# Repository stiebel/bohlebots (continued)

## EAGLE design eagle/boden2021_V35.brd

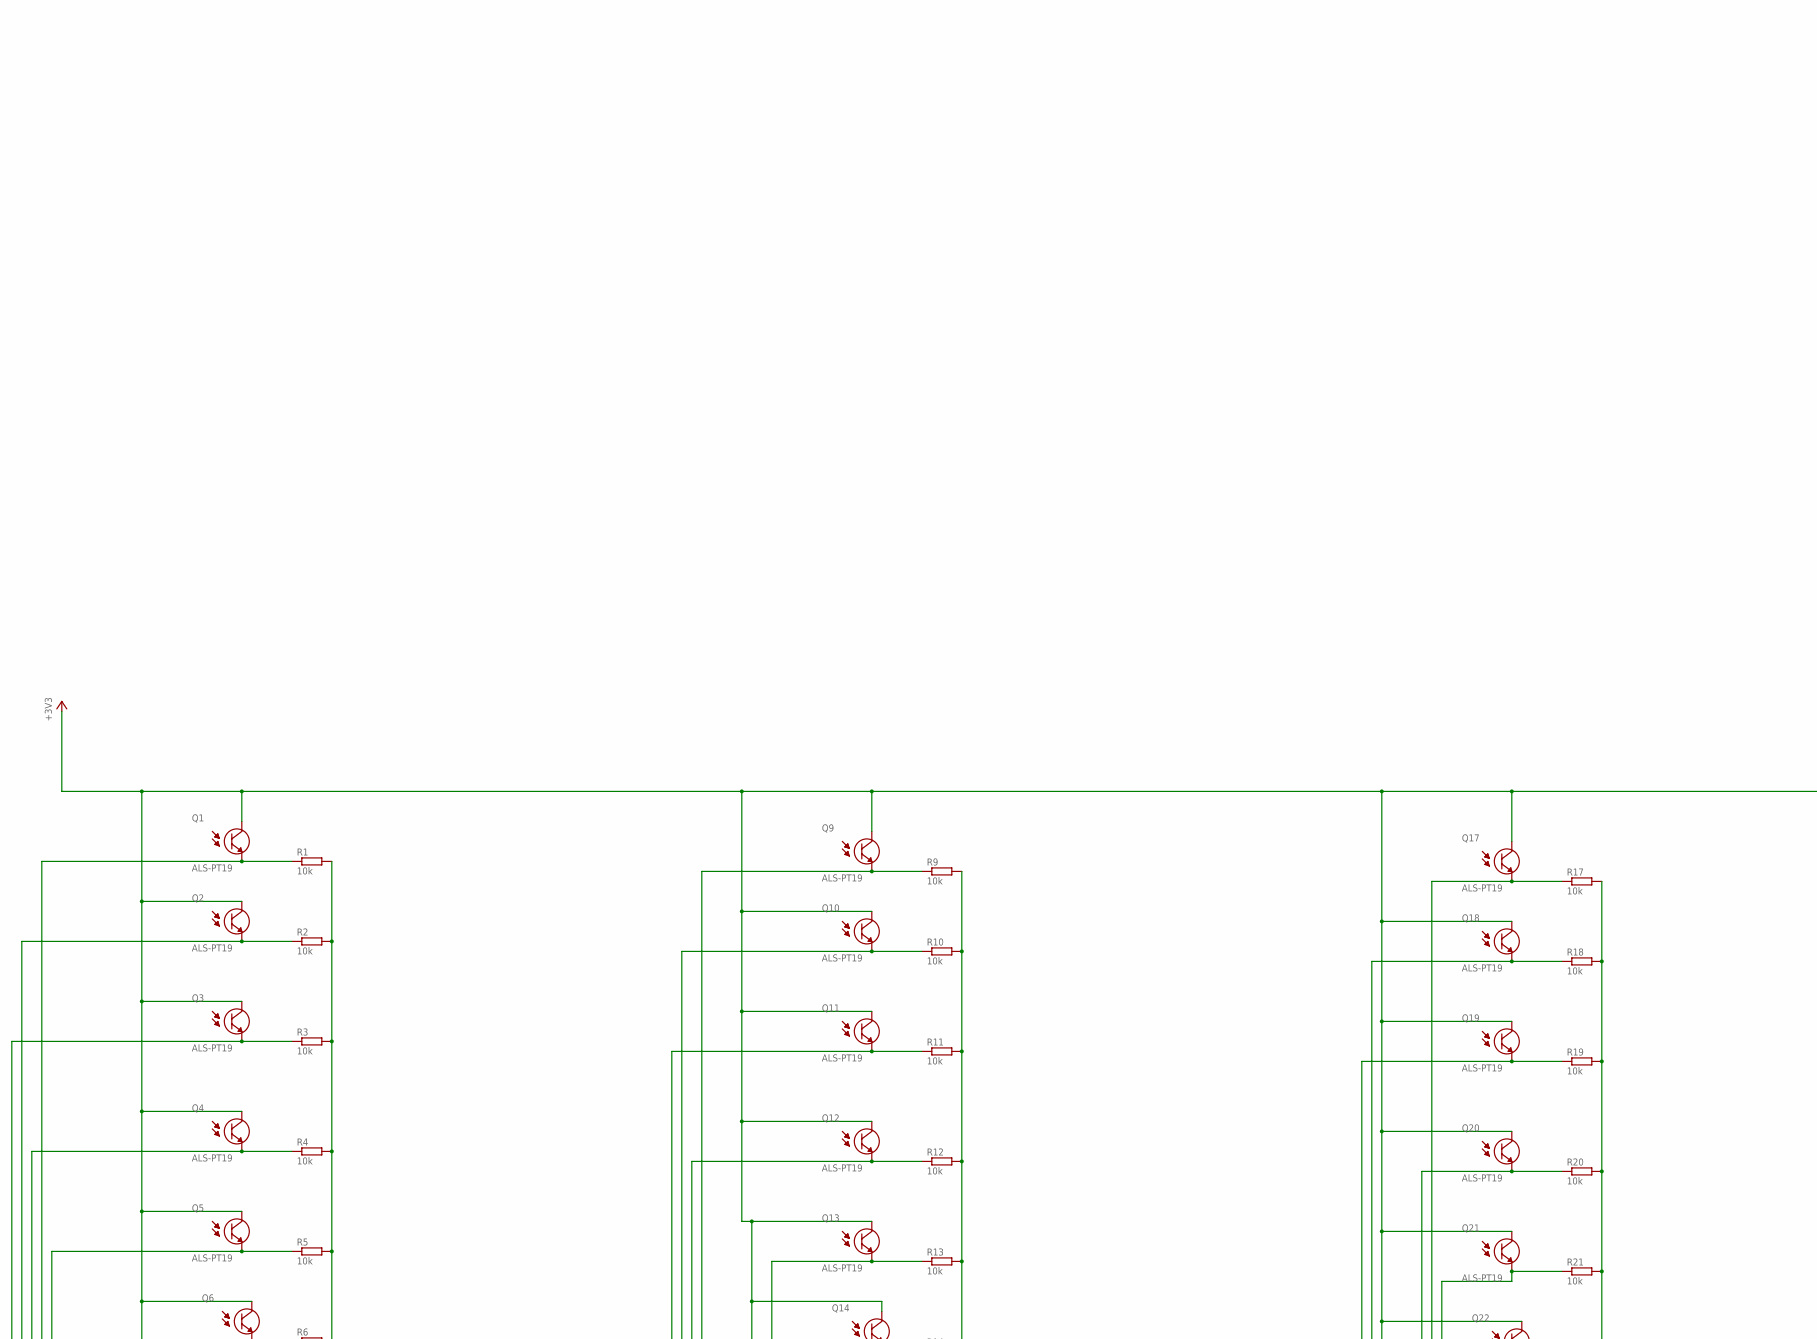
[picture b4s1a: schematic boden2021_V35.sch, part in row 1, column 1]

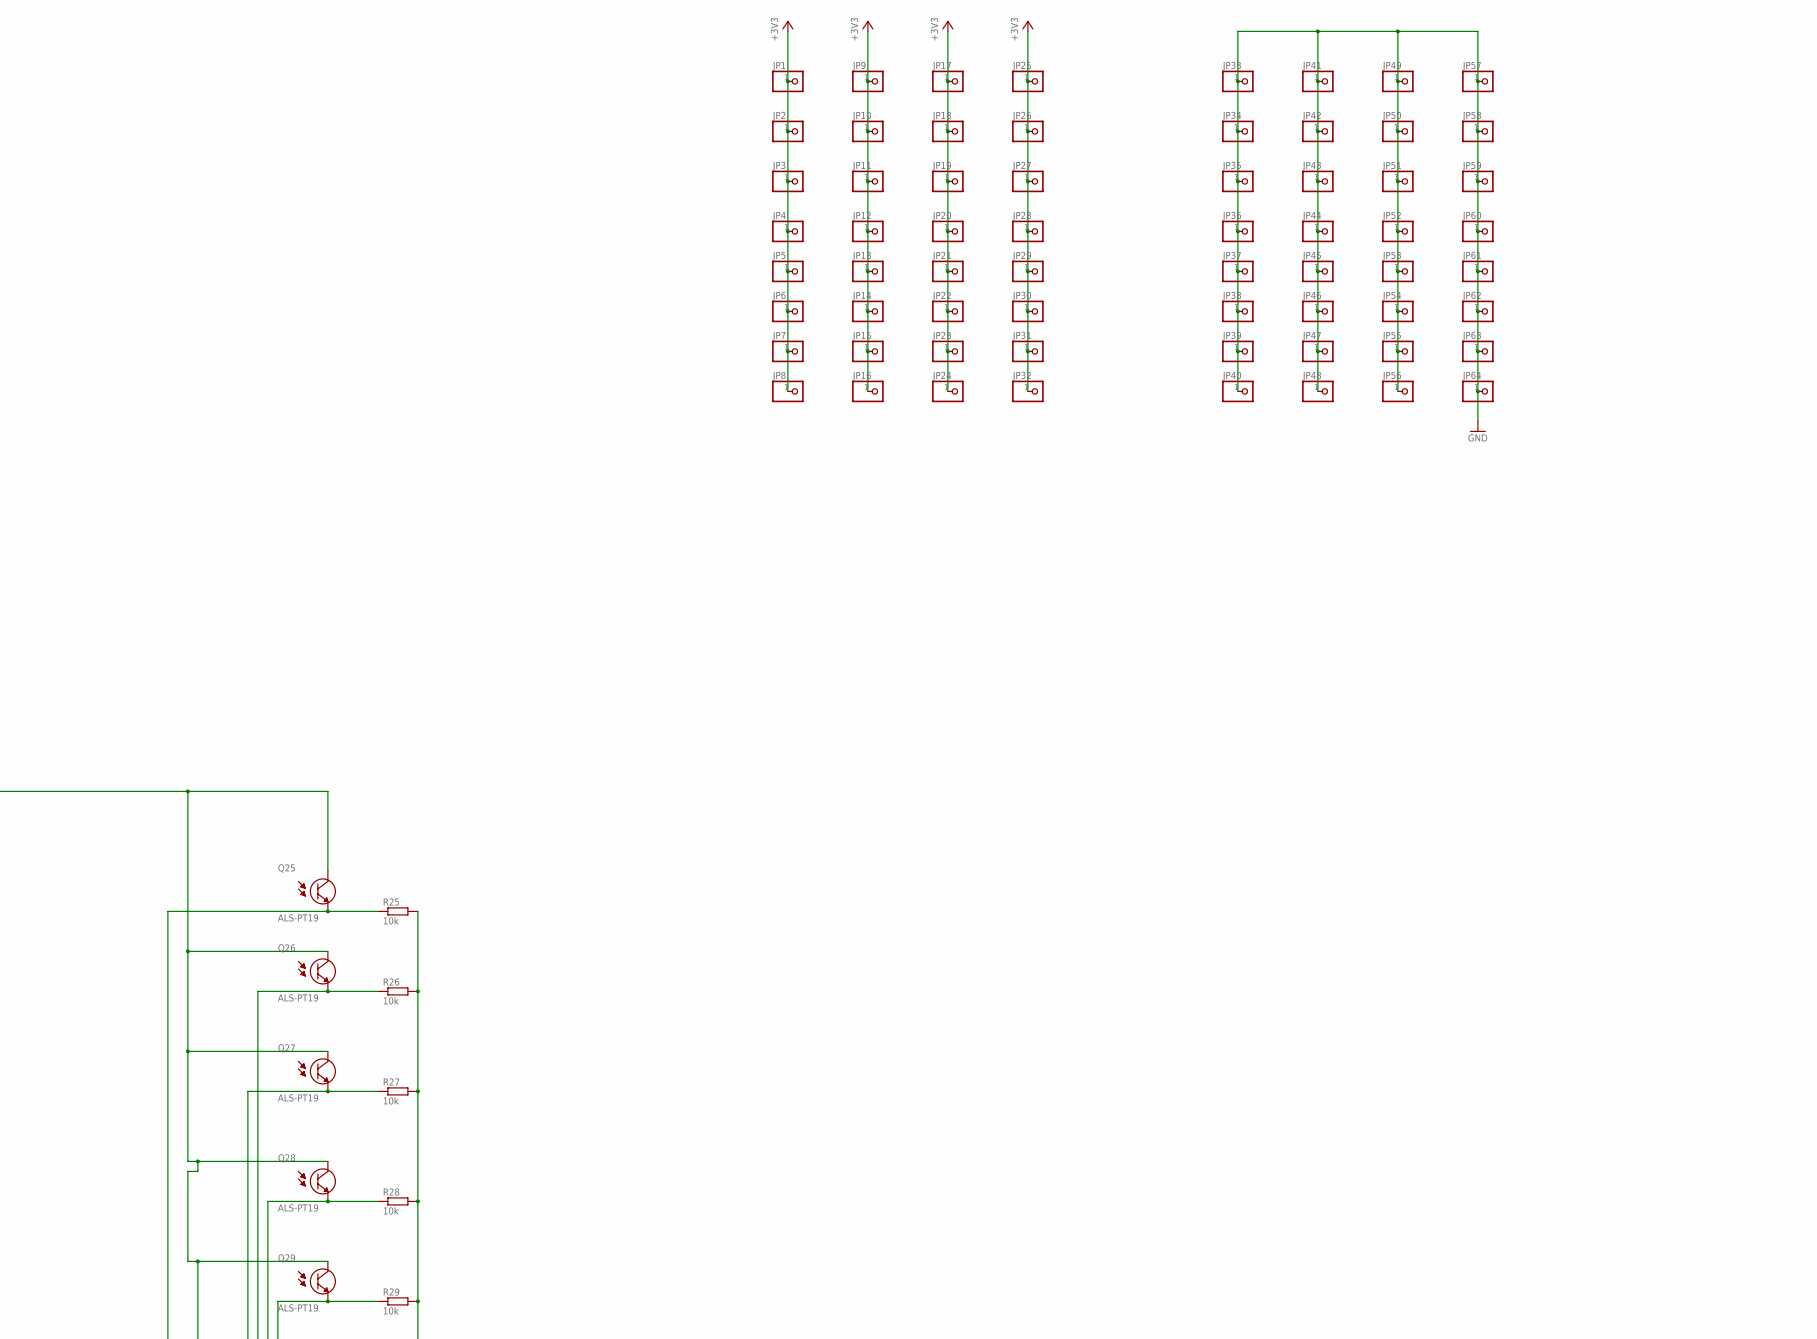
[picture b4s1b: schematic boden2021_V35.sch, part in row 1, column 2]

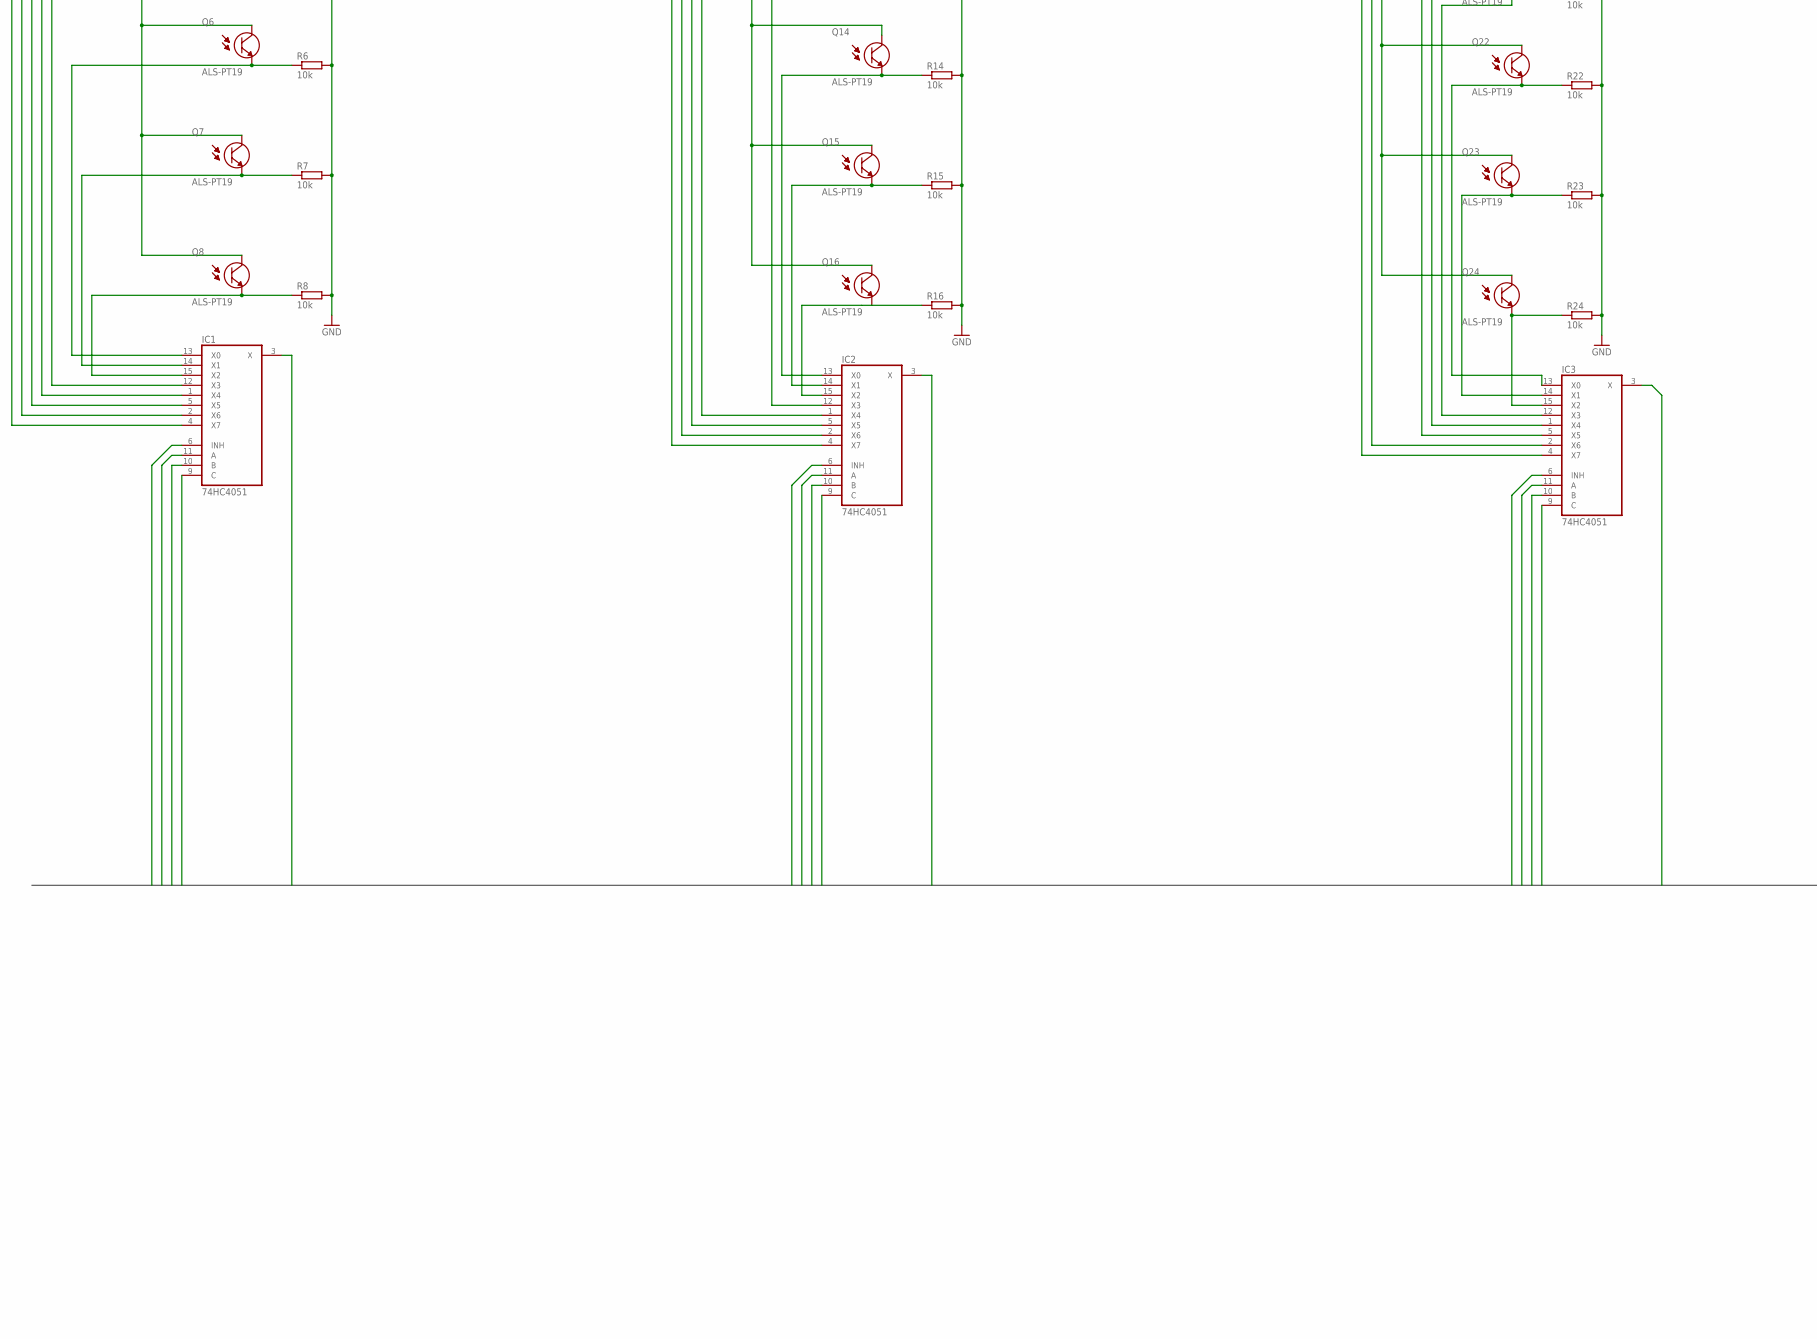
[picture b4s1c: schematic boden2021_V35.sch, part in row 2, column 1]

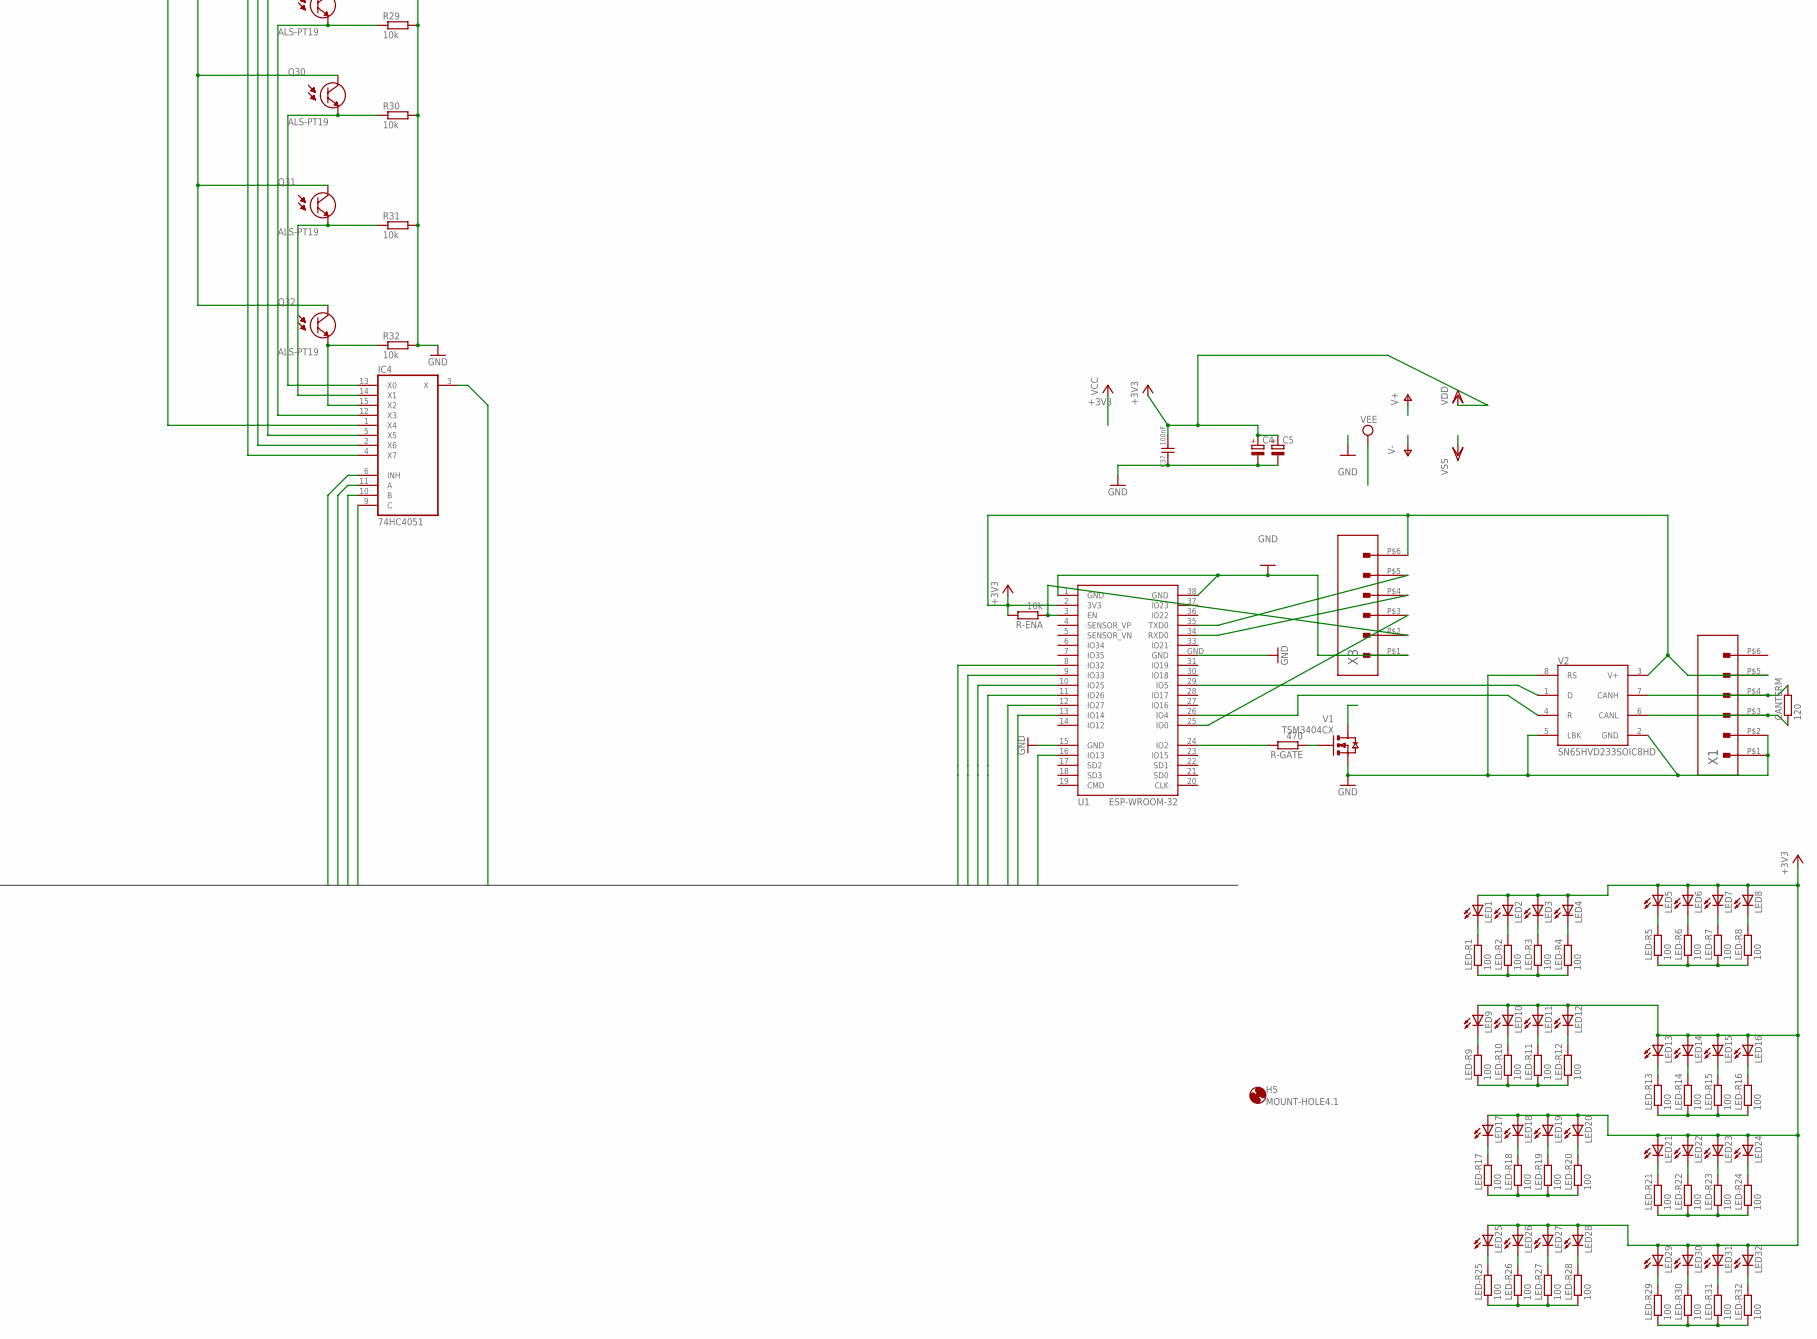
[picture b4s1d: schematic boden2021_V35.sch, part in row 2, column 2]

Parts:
C4, C5: CPOL-EUE2,5-6E; E2,5-6E
C37: 100nF; 0805
CANTERM: 120; R0603
H5: MOUNT-HOLE4.1; 4,1
IC1, IC2, IC3, IC4: 74HC4051; TSSOP-16
JP1, JP2, JP3, JP4, JP5, JP6, JP7, JP8, JP9, JP10, JP11, JP12, JP13, JP14, JP15, JP16, JP17, JP18, JP19, JP20, JP21, JP22, JP23, JP24, JP25, JP26, JP27, JP28, JP29, JP30, JP31, JP32, JP33, JP34, JP35, JP36, JP37, JP38, JP39, JP40, JP41, JP42, JP43, JP44, JP45, JP46, JP47, JP48, JP49, JP50, JP51, JP52, JP53, JP54, JP55, JP56, JP57, JP58, JP59, JP60, JP61, JP62, JP63, JP64: PINHD-1X1; 1X01
LED1, LED2, LED3, LED4, LED5, LED6, LED7, LED8, LED9, LED10, LED11, LED12, LED13, LED14, LED15, LED16, LED17, LED18, LED19, LED20, LED21, LED22, LED23, LED24, LED25, LED26, LED27, LED28, LED29, LED30, LED31, LED32: LEDP-LCC-2; P-LCC-2
LED-R1, LED-R2, LED-R3, LED-R4, LED-R5, LED-R6, LED-R7, LED-R8, LED-R9, LED-R10, LED-R11, LED-R12, LED-R13, LED-R14, LED-R15, LED-R16, LED-R17, LED-R18, LED-R19, LED-R20, LED-R21, LED-R22, LED-R23, LED-R24, LED-R25, LED-R26, LED-R27, LED-R28, LED-R29, LED-R30, LED-R31, LED-R32: 100; R0805
Q1, Q2, Q3, Q4, Q5, Q6, Q7, Q8, Q9, Q10, Q11, Q12, Q13, Q14, Q15, Q16, Q17, Q18, Q19, Q20, Q21, Q22, Q23, Q24, Q25, Q26, Q27, Q28, Q29, Q30, Q31, Q32: ALS-PT19; ALSPT19315CL177TR8
R1, R2, R3, R4, R5, R6, R7, R8, R9, R10, R11, R12, R13, R14, R15, R16, R17, R18, R19, R20, R21, R22, R23, R24, R25, R26, R27, R28, R29, R30, R31, R32: 10k; R0603
R-ENA: 10k; R0603
R-GATE: 470; R0603
U1: ESP-WROOM-32
V1: TSM3404CX; SOT23
V2: SN65HVD233SOIC8HD; SO08
X1, X3: MOLEX104078-0610

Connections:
+3V3: C4.+, C5.+, C37.1, IC1.16 (VCC), IC2.16 (VCC), IC3.16 (VCC), IC4.16 (VCC), JP1.1, JP2.1, JP3.1, JP4.1, JP5.1, JP6.1, JP7.1, JP8.1, JP9.1, JP10.1, JP11.1, JP12.1, JP13.1, JP14.1, JP15.1, JP16.1, JP17.1, JP18.1, JP19.1, JP20.1, JP21.1, JP22.1, JP23.1, JP24.1, JP25.1, JP26.1, JP27.1, JP28.1, JP29.1, JP30.1, JP31.1, JP32.1, LED1.A, LED2.A, LED3.A, LED4.A, LED5.A, LED6.A, LED7.A, LED8.A, LED9.A, LED10.A, LED11.A, LED12.A, LED13.A, LED14.A, LED15.A, LED16.A, LED17.A, LED18.A, LED19.A, LED20.A, LED21.A, LED22.A, LED23.A, LED24.A, LED25.A, LED26.A, LED27.A, LED28.A, LED29.A, LED30.A, LED31.A, LED32.A, Q1.1 (C), Q2.1 (C), Q3.1 (C), Q4.1 (C), Q5.1 (C), Q6.1 (C), Q7.1 (C), Q8.1 (C), Q9.1 (C), Q10.1 (C), Q11.1 (C), Q12.1 (C), Q13.1 (C), Q14.1 (C), Q15.1 (C), Q16.1 (C), Q17.1 (C), Q18.1 (C), Q19.1 (C), Q20.1 (C), Q21.1 (C), Q22.1 (C), Q23.1 (C), Q24.1 (C), Q25.1 (C), Q26.1 (C), Q27.1 (C), Q28.1 (C), Q29.1 (C), Q30.1 (C), Q31.1 (C), Q32.1 (C), R-ENA.2, U1.2 (3V3), V2.3 (V+), X1.P$5 (5), X3.P$6 (6)
A1: IC1.9 (C), IC2.9 (C), IC3.9 (C), IC4.9 (C), U1.16 (IO13)
A2: IC1.10 (B), IC2.10 (B), IC3.10 (B), IC4.10 (B), U1.12 (IO27)
A3: IC1.11 (A), IC2.11 (A), IC3.11 (A), IC4.11 (A), U1.13 (IO14)
D1: IC2.3 (X), U1.8 (IO32)
D2: IC1.3 (X), U1.9 (IO33)
D3: IC3.3 (X), U1.10 (IO25)
D4: IC4.3 (X), U1.11 (IO26)
GND: C4.-, C5.-, C37.2, IC1.6 (INH), IC1.7 (VEE), IC1.8 (GND), IC2.6 (INH), IC2.7 (VEE), IC2.8 (GND), IC3.6 (INH), IC3.7 (VEE), IC3.8 (GND), IC4.6 (INH), IC4.7 (VEE), IC4.8 (GND), JP33.1, JP34.1, JP35.1, JP36.1, JP37.1, JP38.1, JP39.1, JP40.1, JP41.1, JP42.1, JP43.1, JP44.1, JP45.1, JP46.1, JP47.1, JP48.1, JP49.1, JP50.1, JP51.1, JP52.1, JP53.1, JP54.1, JP55.1, JP56.1, JP57.1, JP58.1, JP59.1, JP60.1, JP61.1, JP62.1, JP63.1, JP64.1, R1.2, R2.2, R3.2, R4.2, R5.2, R6.2, R7.2, R8.2, R9.2, R10.2, R11.2, R12.2, R13.2, R14.2, R15.2, R16.2, R17.2, R18.2, R19.2, R20.2, R21.2, R22.2, R23.2, R24.2, R25.2, R26.2, R27.2, R28.2, R29.2, R30.2, R31.2, R32.2, U1.1 (GND), U1.15 (GND), U1.38 (GND), U1.GND, V1.S, V2.2 (GND), V2.5 (LBK), V2.8 (RS), X1.P$1 (1), X1.P$2 (2), X3.P$1 (1)
LED: LED-R1.1, LED-R2.1, LED-R3.1, LED-R4.1, LED-R5.1, LED-R6.1, LED-R7.1, LED-R8.1, LED-R9.1, LED-R10.1, LED-R11.1, LED-R12.1, LED-R13.1, LED-R14.1, LED-R15.1, LED-R16.1, LED-R17.1, LED-R18.1, LED-R19.1, LED-R20.1, LED-R21.1, LED-R22.1, LED-R23.1, LED-R24.1, LED-R25.1, LED-R26.1, LED-R27.1, LED-R28.1, LED-R29.1, LED-R30.1, LED-R31.1, LED-R32.1, V1.D
LED-BASE: R-GATE.1, V1.G
LED-SCHALT: R-GATE.2, U1.24 (IO2)
unnamed: LED5.C, LED-R5.2
unnamed: LED6.C, LED-R6.2
unnamed: LED7.C, LED-R7.2
unnamed: LED8.C, LED-R8.2
unnamed: LED9.C, LED-R9.2
unnamed: LED10.C, LED-R10.2
unnamed: LED11.C, LED-R11.2
unnamed: LED12.C, LED-R12.2
unnamed: LED1.C, LED-R1.2
unnamed: LED2.C, LED-R2.2
unnamed: LED3.C, LED-R3.2
unnamed: LED4.C, LED-R4.2
unnamed: LED13.C, LED-R13.2
unnamed: LED14.C, LED-R14.2
unnamed: LED15.C, LED-R15.2
unnamed: LED16.C, LED-R16.2
unnamed: LED17.C, LED-R17.2
unnamed: LED18.C, LED-R18.2
unnamed: LED19.C, LED-R19.2
unnamed: LED20.C, LED-R20.2
unnamed: LED21.C, LED-R21.2
unnamed: LED22.C, LED-R22.2
unnamed: LED23.C, LED-R23.2
unnamed: LED24.C, LED-R24.2
unnamed: LED25.C, LED-R25.2
unnamed: LED26.C, LED-R26.2
unnamed: LED27.C, LED-R27.2
unnamed: LED28.C, LED-R28.2
unnamed: LED29.C, LED-R29.2
unnamed: LED30.C, LED-R30.2
unnamed: LED31.C, LED-R31.2
unnamed: LED32.C, LED-R32.2
unnamed: R-ENA.1, U1.3 (EN), X3.P$2 (2)
unnamed: IC1.13 (X0), Q6.2 (E), R6.1
unnamed: U1.25 (IO0), X3.P$3 (3)
unnamed: IC3.14 (X1), Q23.2 (E), R23.1
unnamed: IC3.13 (X0), Q22.2 (E), R22.1
unnamed: IC1.12 (X3), Q5.2 (E), R5.1
unnamed: IC1.14 (X1), Q7.2 (E), R7.1
unnamed: IC1.15 (X2), Q8.2 (E), R8.1
unnamed: IC3.12 (X3), Q21.2 (E), R21.1
unnamed: IC4.4 (X7), Q27.2 (E), R27.1
unnamed: IC1.1 (X4), Q1.2 (E), R1.1
unnamed: IC1.5 (X5), Q4.2 (E), R4.1
unnamed: IC1.2 (X6), Q2.2 (E), R2.1
unnamed: IC1.4 (X7), Q3.2 (E), R3.1
unnamed: IC2.15 (X2), Q16.2 (E), R16.1
unnamed: IC2.14 (X1), Q15.2 (E), R15.1
unnamed: IC2.13 (X0), Q14.2 (E), R14.1
unnamed: IC2.12 (X3), Q13.2 (E), R13.1
unnamed: IC2.1 (X4), Q9.2 (E), R9.1
unnamed: IC2.5 (X5), Q12.2 (E), R12.1
unnamed: IC2.4 (X7), Q11.2 (E), R11.1
unnamed: IC2.2 (X6), Q10.2 (E), R10.1
unnamed: IC3.15 (X2), Q24.2 (E), R24.1
unnamed: IC4.2 (X6), Q26.2 (E), R26.1
unnamed: IC3.1 (X4), Q17.2 (E), R17.1
unnamed: IC3.5 (X5), Q20.2 (E), R20.1
unnamed: IC3.2 (X6), Q18.2 (E), R18.1
unnamed: IC3.4 (X7), Q19.2 (E), R19.1
unnamed: IC4.15 (X2), Q32.2 (E), R32.1
unnamed: IC4.14 (X1), Q31.2 (E), R31.1
unnamed: IC4.13 (X0), Q30.2 (E), R30.1
unnamed: IC4.12 (X3), Q29.2 (E), R29.1
unnamed: IC4.1 (X4), Q25.2 (E), R25.1
unnamed: IC4.5 (X5), Q28.2 (E), R28.1
unnamed: U1.26 (IO4), V2.4 (R)
unnamed: U1.29 (IO5), V2.1 (D)
unnamed: CANTERM.2, V2.7 (CANH), X1.P$4 (4)
unnamed: CANTERM.1, V2.6 (CANL), X1.P$3 (3)
RX: U1.34 (RXD0), X3.P$4 (4)
TX: U1.35 (TXD0), X3.P$5 (5)

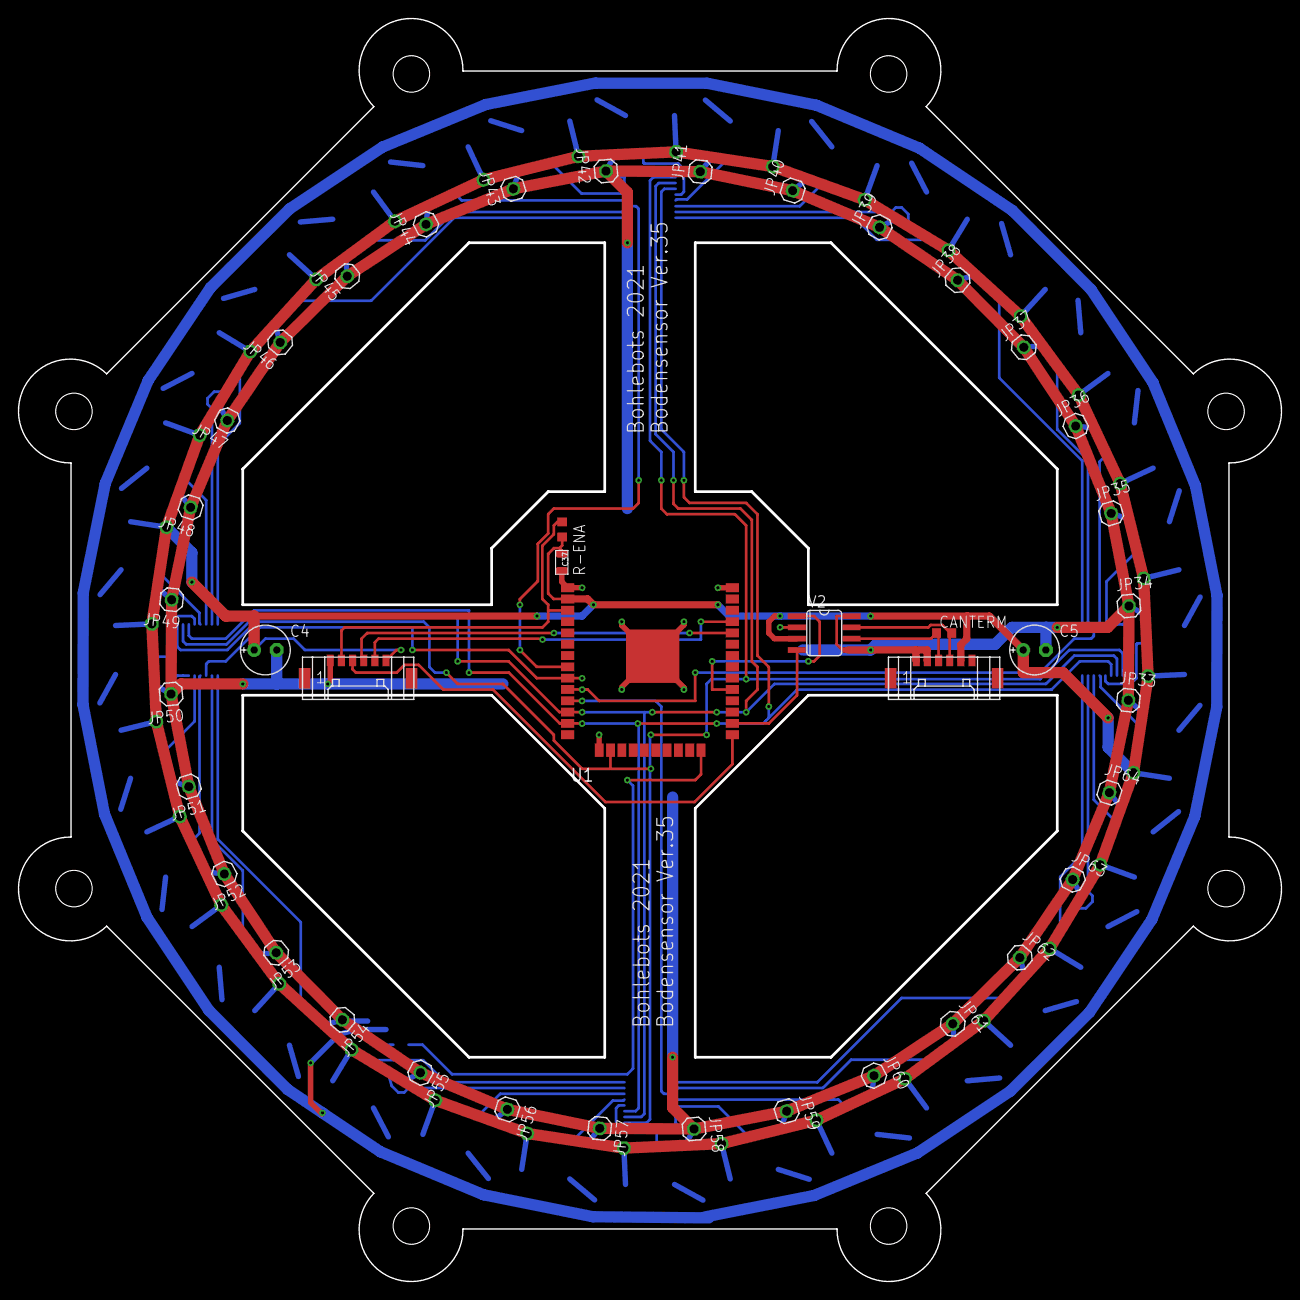
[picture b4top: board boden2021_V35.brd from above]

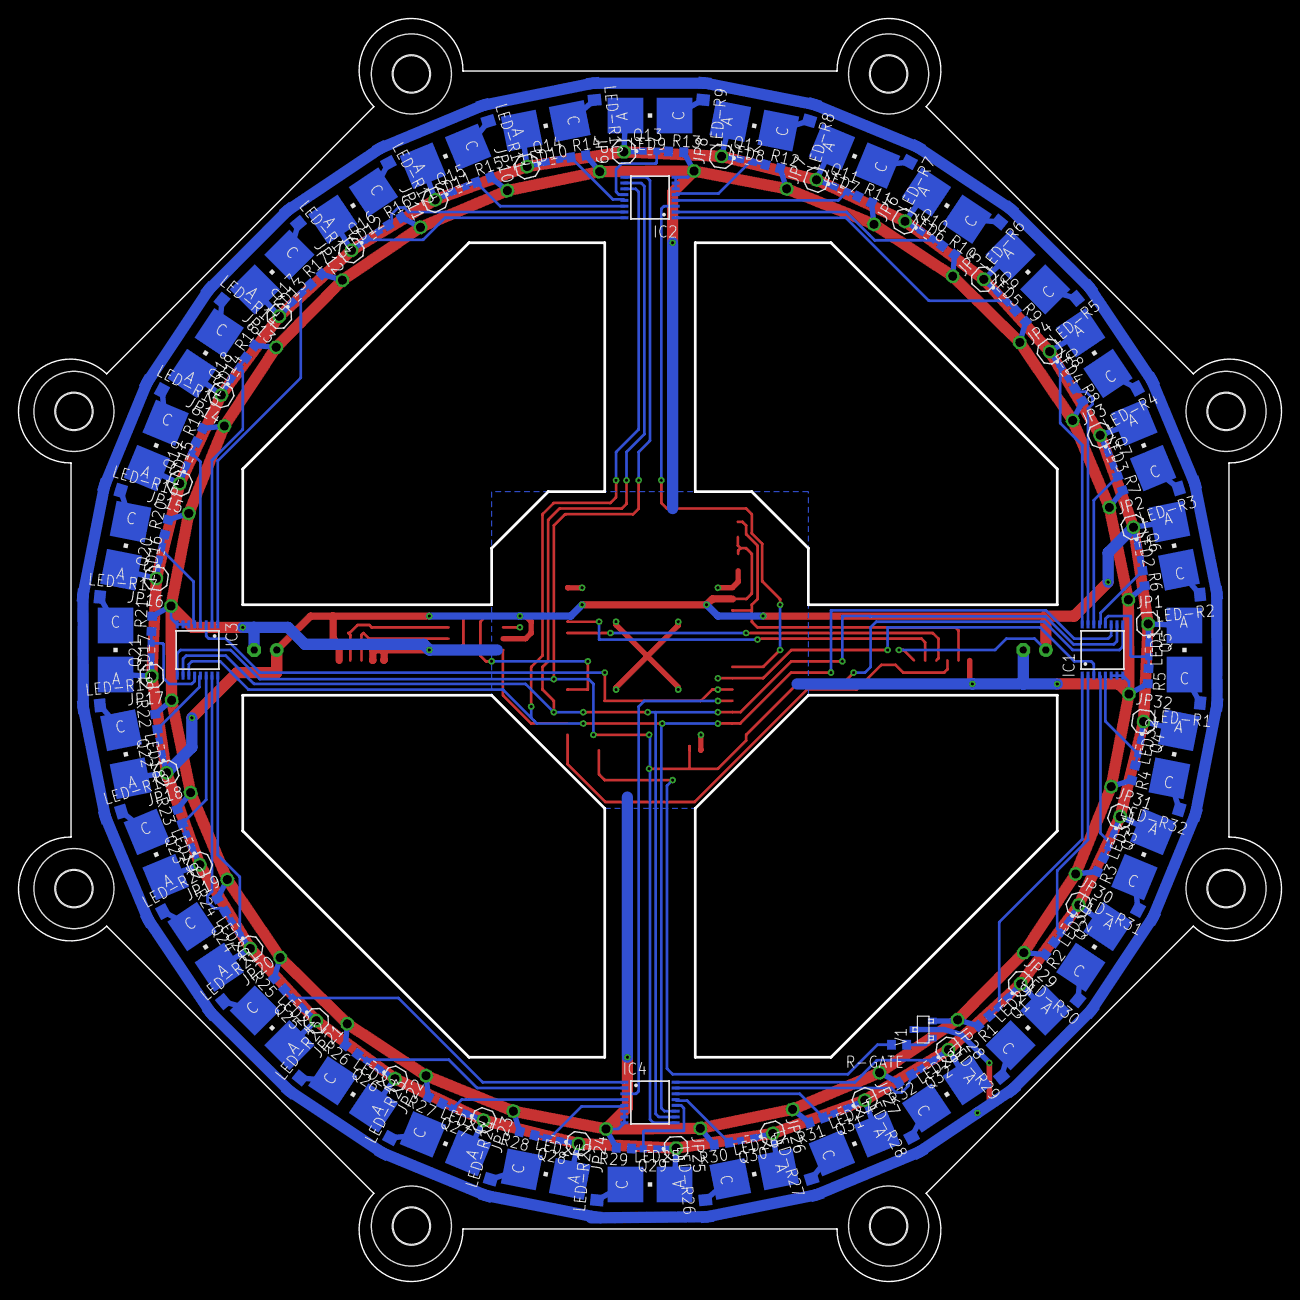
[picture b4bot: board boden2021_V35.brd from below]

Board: 2 copper layers, 141.8 x 141.8 mm, 215 parts (174 on the bottom side), 84 nets.

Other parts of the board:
H1, H2, H3, H4, H6, H7, H8: MOUNT-HOLE4.1; 4,1

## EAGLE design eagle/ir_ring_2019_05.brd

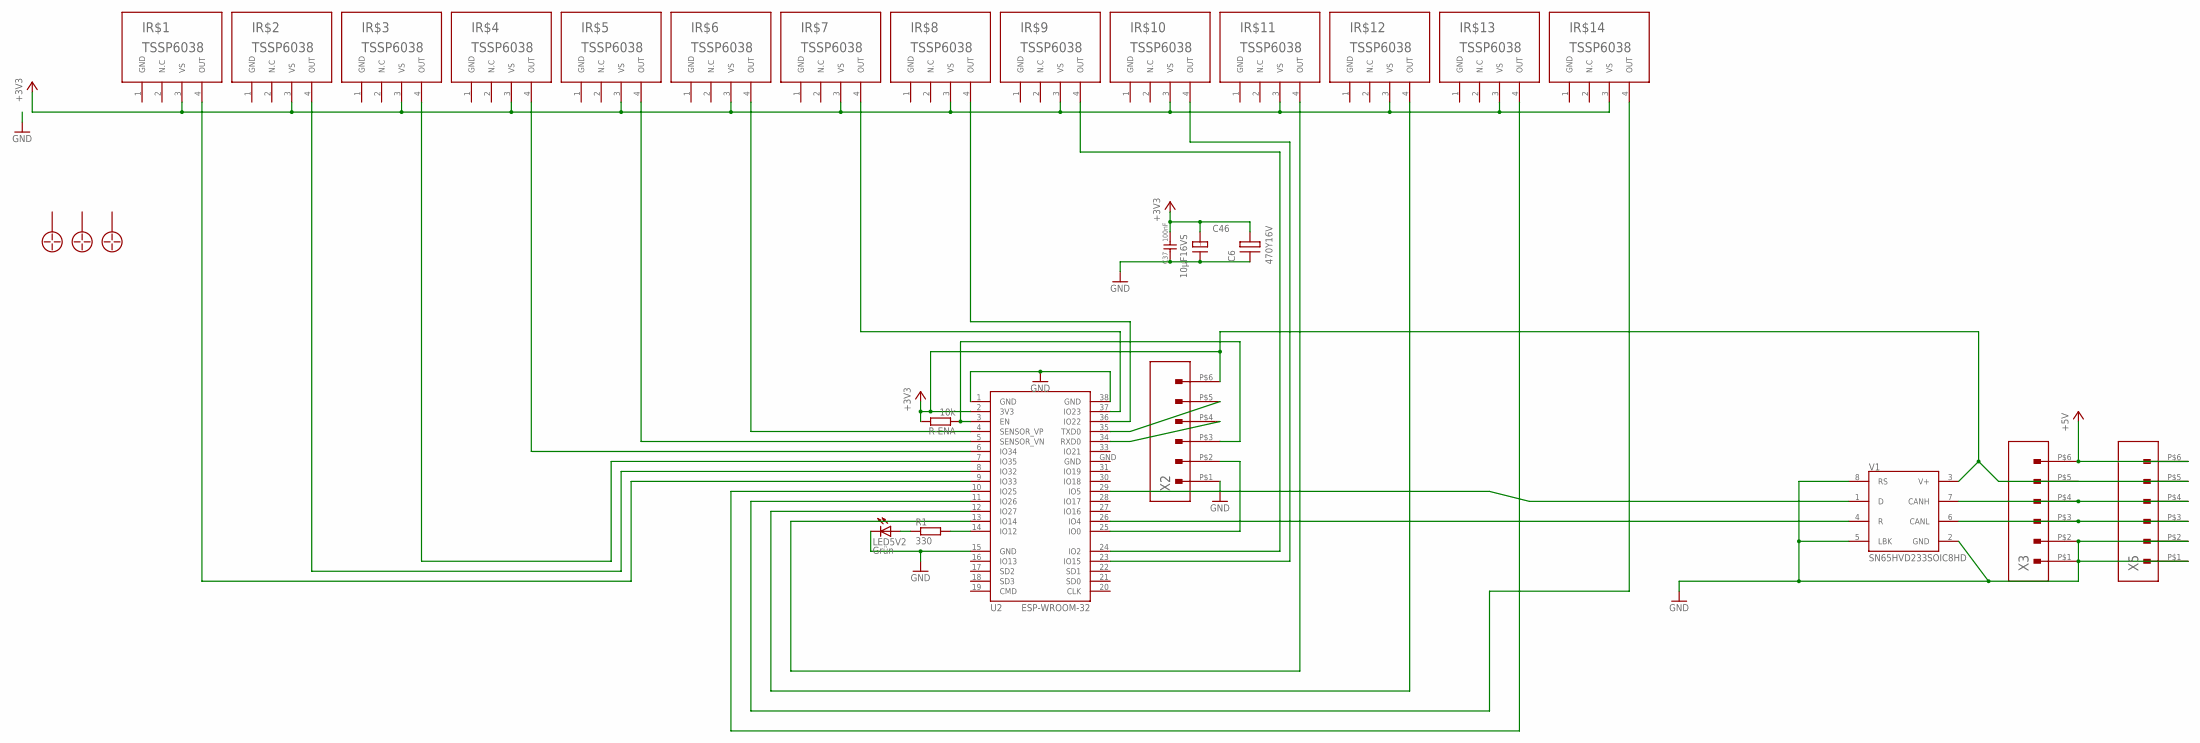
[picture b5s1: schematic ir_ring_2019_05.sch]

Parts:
C6: 470Y16V; 150CLZ-1010
C37: 100nF; 0805
C46: 10µF16VS; TANTALC
IR$1, IR$2, IR$3, IR$4, IR$5, IR$6, IR$7, IR$8, IR$9, IR$10, IR$11, IR$12, IR$13, IR$14: TSSP6038
LED5V2: Grün; CHIP-LED0805
PM1, PM2, PM3: SMD-PASSER-1MMR
R1: 330; R0805
R-ENA: 10k; R0805
U2: ESP-WROOM-32
V1: SN65HVD233SOIC8HD; SO08
X2, X3, X5: MOLEX104078-0610

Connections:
+3V3: C6.+, C37.1, C46.+, IR$1.3 (VS), IR$2.3 (VS), IR$3.3 (VS), IR$4.3 (VS), IR$5.3 (VS), IR$6.3 (VS), IR$7.3 (VS), IR$8.3 (VS), IR$9.3 (VS), IR$10.3 (VS), IR$11.3 (VS), IR$12.3 (VS), IR$13.3 (VS), IR$14.3 (VS), R-ENA.2, U2.2 (3V3), V1.3 (V+), X2.P$6 (6), X3.P$5 (5), X5.P$5 (5)
+5V: X3.P$6 (6), X5.P$6 (6)
GND: C6.-, C37.2, C46.-, IR$1.1 (GND), IR$2.1 (GND), IR$3.1 (GND), IR$4.1 (GND), IR$5.1 (GND), IR$6.1 (GND), IR$7.1 (GND), IR$8.1 (GND), IR$9.1 (GND), IR$10.1 (GND), IR$11.1 (GND), IR$12.1 (GND), IR$13.1 (GND), IR$14.1 (GND), LED5V2.C, U2.1 (GND), U2.15 (GND), U2.38 (GND), U2.GND, V1.2 (GND), V1.5 (LBK), V1.8 (RS), X2.P$1 (1), X3.P$1 (1), X3.P$2 (2), X5.P$1 (1), X5.P$2 (2)
unnamed: IR$3.4 (OUT), U2.7 (IO35)
unnamed: IR$2.4 (OUT), U2.8 (IO32)
unnamed: IR$1.4 (OUT), U2.9 (IO33)
unnamed: IR$12.4 (OUT), U2.12 (IO27)
unnamed: IR$11.4 (OUT), U2.13 (IO14)
unnamed: IR$10.4 (OUT), U2.23 (IO15)
unnamed: IR$9.4 (OUT), U2.24 (IO2)
unnamed: IR$13.4 (OUT), U2.10 (IO25)
unnamed: IR$6.4 (OUT), U2.4 (SENSOR_VP)
unnamed: IR$5.4 (OUT), U2.5 (SENSOR_VN)
unnamed: IR$4.4 (OUT), U2.6 (IO34)
unnamed: IR$7.4 (OUT), U2.37 (IO23)
unnamed: IR$8.4 (OUT), U2.36 (IO22)
unnamed: U2.26 (IO4), V1.4 (R)
unnamed: U2.29 (IO5), V1.1 (D)
unnamed: V1.7 (CANH), X3.P$4 (4), X5.P$4 (4)
unnamed: V1.6 (CANL), X3.P$3 (3), X5.P$3 (3)
unnamed: LED5V2.A, R1.1
unnamed: R1.2, U2.14 (IO12)
unnamed: R-ENA.1, U2.3 (EN), X2.P$3 (3)
unnamed: U2.25 (IO0), X2.P$2 (2)
RX: U2.34 (RXD0), X2.P$4 (4)
TX: U2.35 (TXD0), X2.P$5 (5)
WS6: IR$14.4 (OUT), U2.11 (IO26)

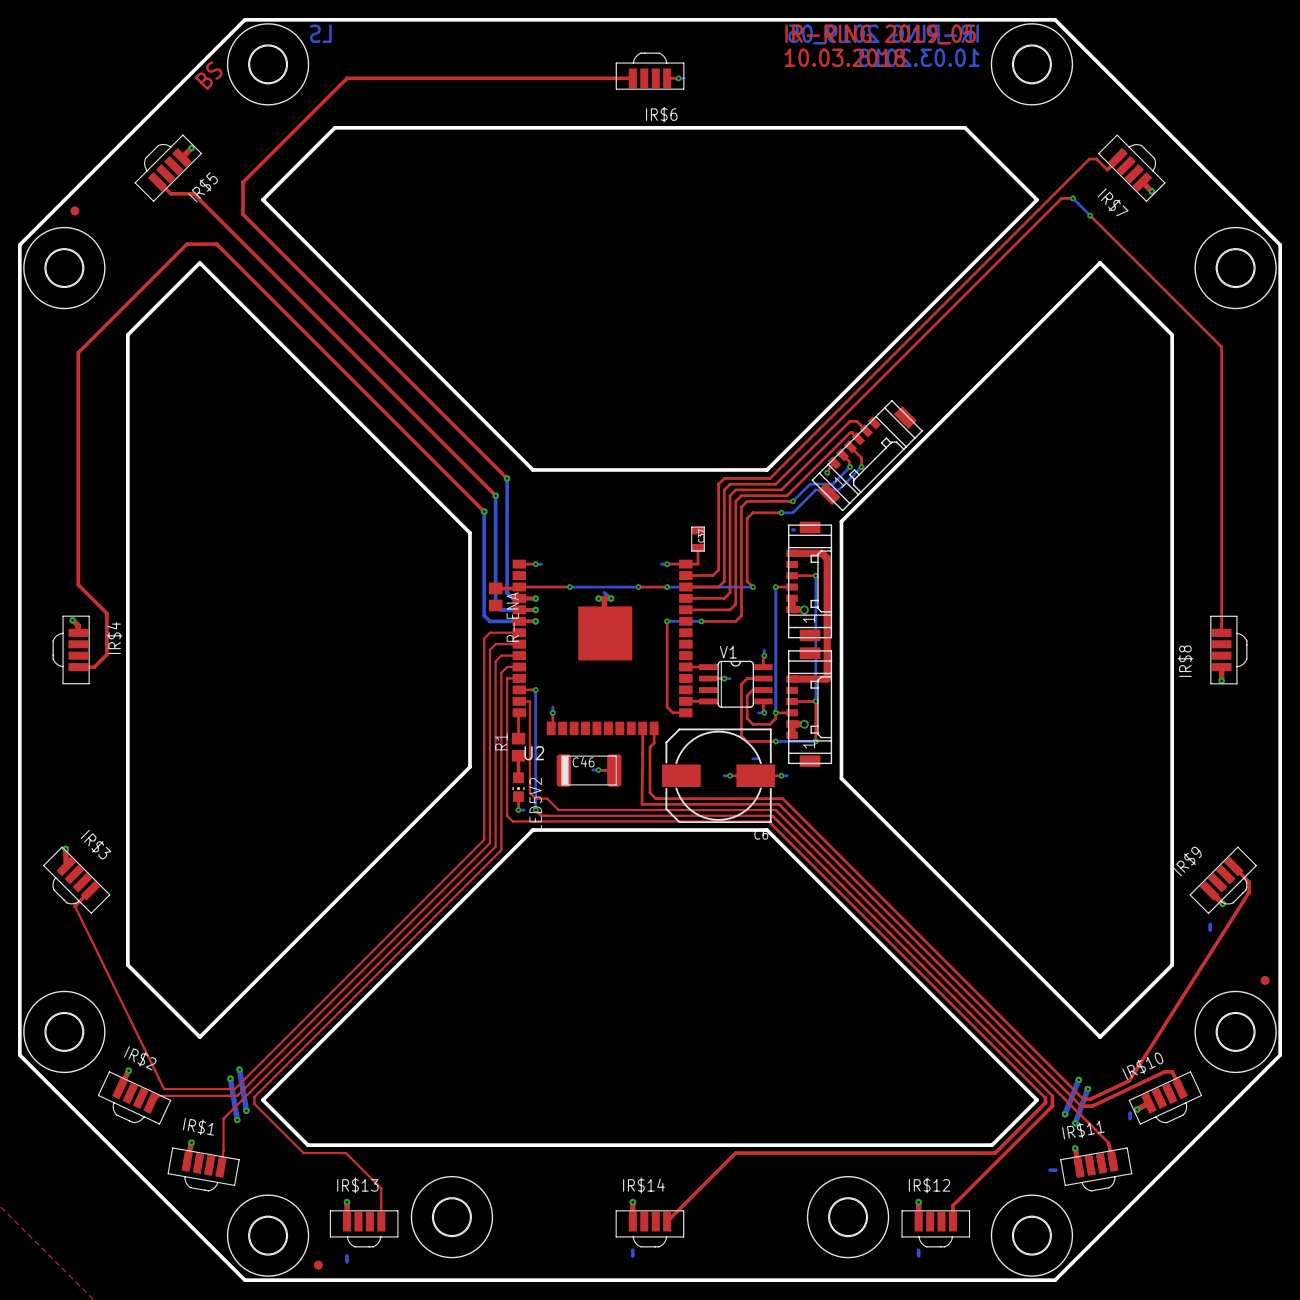
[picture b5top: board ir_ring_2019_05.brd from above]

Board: 2 copper layers, 140.0 x 140.0 mm, 38 parts (0 on the bottom side), 27 nets.

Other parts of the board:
H1, H2, H3, H4, H5, H6, H7, H8, H9, H10: MOUNT-HOLE4.1; 4,1

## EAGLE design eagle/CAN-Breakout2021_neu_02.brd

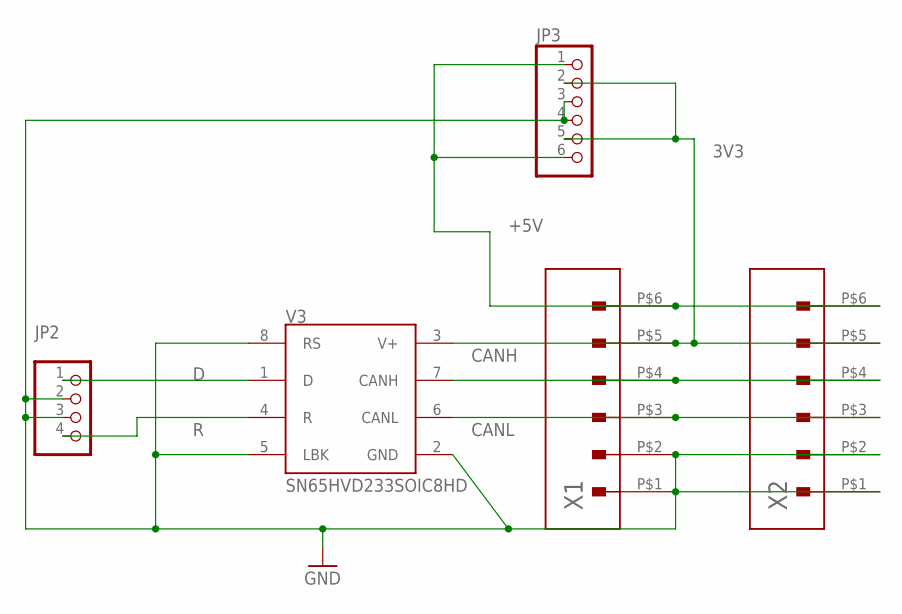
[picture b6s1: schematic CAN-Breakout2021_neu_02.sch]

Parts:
JP2: PINHD-1X4; 1X04
JP3: PINHD-1X6; 1X06
V3: SN65HVD233SOIC8HD; SO08
X1, X2: MOLEX104078-0610

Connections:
3V3: JP3.2, JP3.5, V3.3 (V+), X1.P$5 (5), X2.P$5 (5)
+5V: JP3.1, JP3.6, X1.P$6 (6), X2.P$6 (6)
CANH: V3.7 (CANH), X1.P$4 (4), X2.P$4 (4)
CANL: V3.6 (CANL), X1.P$3 (3), X2.P$3 (3)
D: JP2.1, V3.1 (D)
GND: JP2.2, JP2.3, JP3.3, JP3.4, V3.2 (GND), V3.5 (LBK), V3.8 (RS), X1.P$1 (1), X1.P$2 (2), X2.P$1 (1), X2.P$2 (2)
R: JP2.4, V3.4 (R)

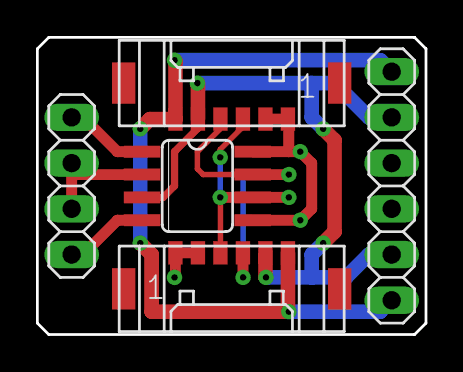
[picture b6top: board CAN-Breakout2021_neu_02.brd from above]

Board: 2 copper layers, 21.6 x 16.5 mm, 5 parts (0 on the bottom side), 7 nets.
